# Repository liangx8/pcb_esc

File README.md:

# Electronic speed control(ESC)

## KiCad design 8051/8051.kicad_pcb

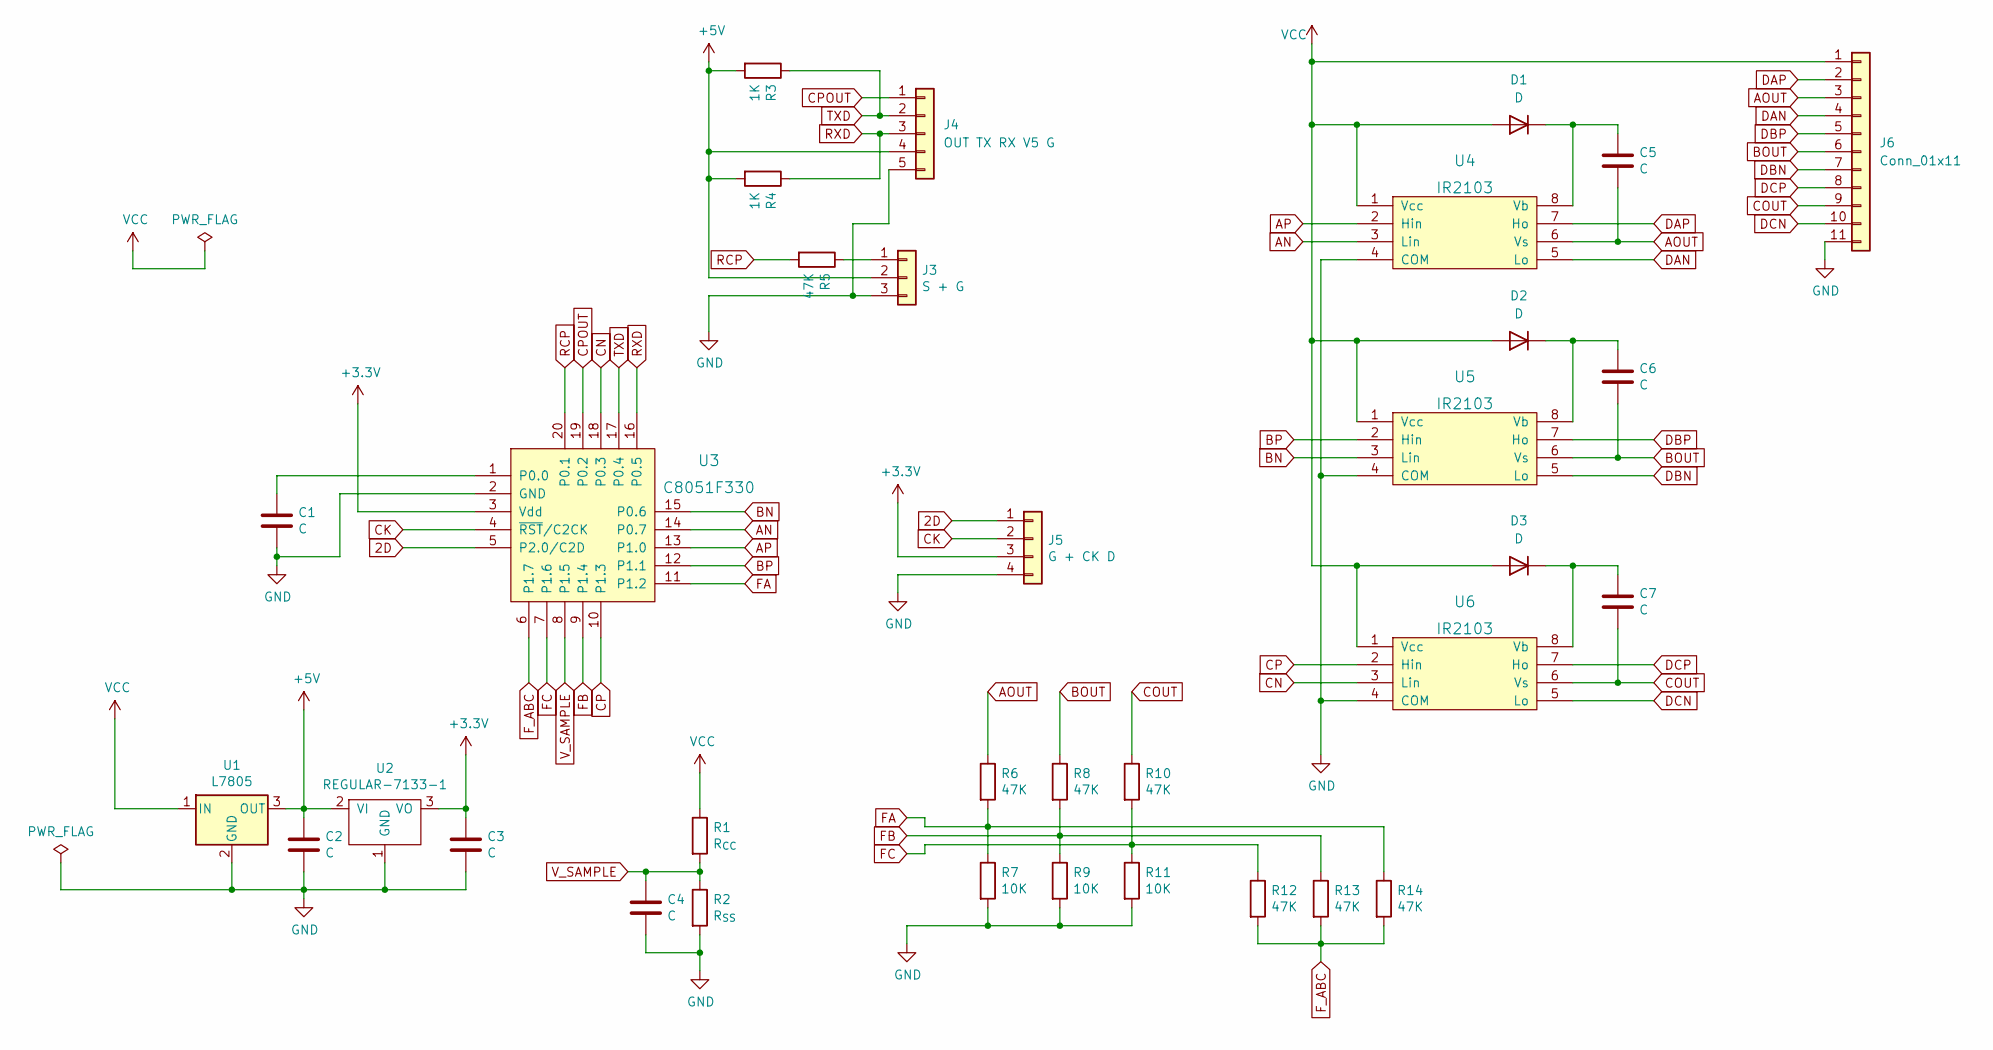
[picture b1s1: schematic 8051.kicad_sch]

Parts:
C1, C2, C3, C4: C; 0603_p1.7xpad1.0
C5, C6, C7: C; 0805_p2.0xpad1.0
D1, D2, D3: D; 0805_p2.0xpad1.0
J3: S + G; PinHeader_1x03_P2.54mm_Vertical
J4: OUT TX RX V5 G; PinHeader_1x05_P2.54mm_Vertical
J5: G + CK D; CONN4-P2.54-DR1.0-W1.5
J6: Conn_01x11; PinHeader_1x11_P2.54mm_Vertical
R1: R_{CC}; 0603_p1.7xpad1.0
R2: R_{SS}; 0603_p1.7xpad1.0
R3, R4: 1K; 0603_p1.7xpad1.0
R5, R6, R8, R10, R12, R13, R14: 47K; 0603_p1.7xpad1.0
R7, R9, R11: 10K; 0603_p1.7xpad1.0
U1: L7805; TO-252-2
U2: REGULAR-7133-1; SOT-89-3_Handsoldering
U3: C8051F330; QFN-20_EP_4x4_Pitch0.5mm
U4, U5, U6: IR2103; SOIC-8

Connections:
2D: J5.1, U3.5 (P2.0/C2D)
+3V3: C3.1, J5.3, U2.3 (VO), U3.3 (Vdd)
+5V: C2.1, J3.2, J4.4, R3.2, R4.2, U1.3 (OUT), U2.2 (VI)
AN: U3.14 (P0.7), U4.3 (Lin)
AOUT: C5.2, J6.3, R6.1, U4.6 (Vs)
AP: U3.13 (P1.0), U4.2 (Hin)
BN: U3.15 (P0.6), U5.3 (Lin)
BOUT: C6.2, J6.6, R8.1, U5.6 (Vs)
BP: U3.12 (P1.1), U5.2 (Hin)
CK: J5.2, U3.4 (~RST/C2CK)
CN: U3.18 (P0.3), U6.3 (Lin)
COUT: C7.2, J6.9, R10.1, U6.6 (Vs)
CP: U3.10 (P1.3), U6.2 (Hin)
CPOUT: J4.1, U3.19 (P0.2)
DAN: J6.4, U4.5 (Lo)
DAP: J6.2, U4.7 (Ho)
DBN: J6.7, U5.5 (Lo)
DBP: J6.5, U5.7 (Ho)
DCN: J6.10, U6.5 (Lo)
DCP: J6.8, U6.7 (Ho)
FA: R6.2, R7.1, R14.1, U3.11 (P1.2)
FB: R8.2, R9.1, R13.1, U3.9 (P1.4)
FC: R10.2, R11.1, R12.1, U3.7 (P1.6)
F_ABC: R12.2, R13.2, R14.2, U3.6 (P1.7)
GND: C1.2, C2.2, C3.2, C4.2, J3.3, J4.5, J5.4, J6.11, R2.2, R7.2, R9.2, R11.2, U1.2 (GND), U2.1 (GND), U3.2 (GND), U4.4 (COM), U5.4 (COM), U6.4 (COM)
unnamed: C1.1, U3.1 (P0.0)
unnamed: C5.1, D1.1 (K), U4.8 (Vb)
unnamed: C6.1, D2.1 (K), U5.8 (Vb)
unnamed: C7.1, D3.1 (K), U6.8 (Vb)
unnamed: J3.1, R5.1
RCP: R5.2, U3.20 (P0.1)
RXD: J4.3, R4.1, U3.16 (P0.5)
TXD: J4.2, R3.1, U3.17 (P0.4)
VCC: D1.2 (A), D2.2 (A), D3.2 (A), J6.1, R1.1, U1.1 (IN), U4.1 (Vcc), U5.1 (Vcc), U6.1 (Vcc)
V_SAMPLE: C4.1, R1.2, R2.1, U3.8 (P1.5)

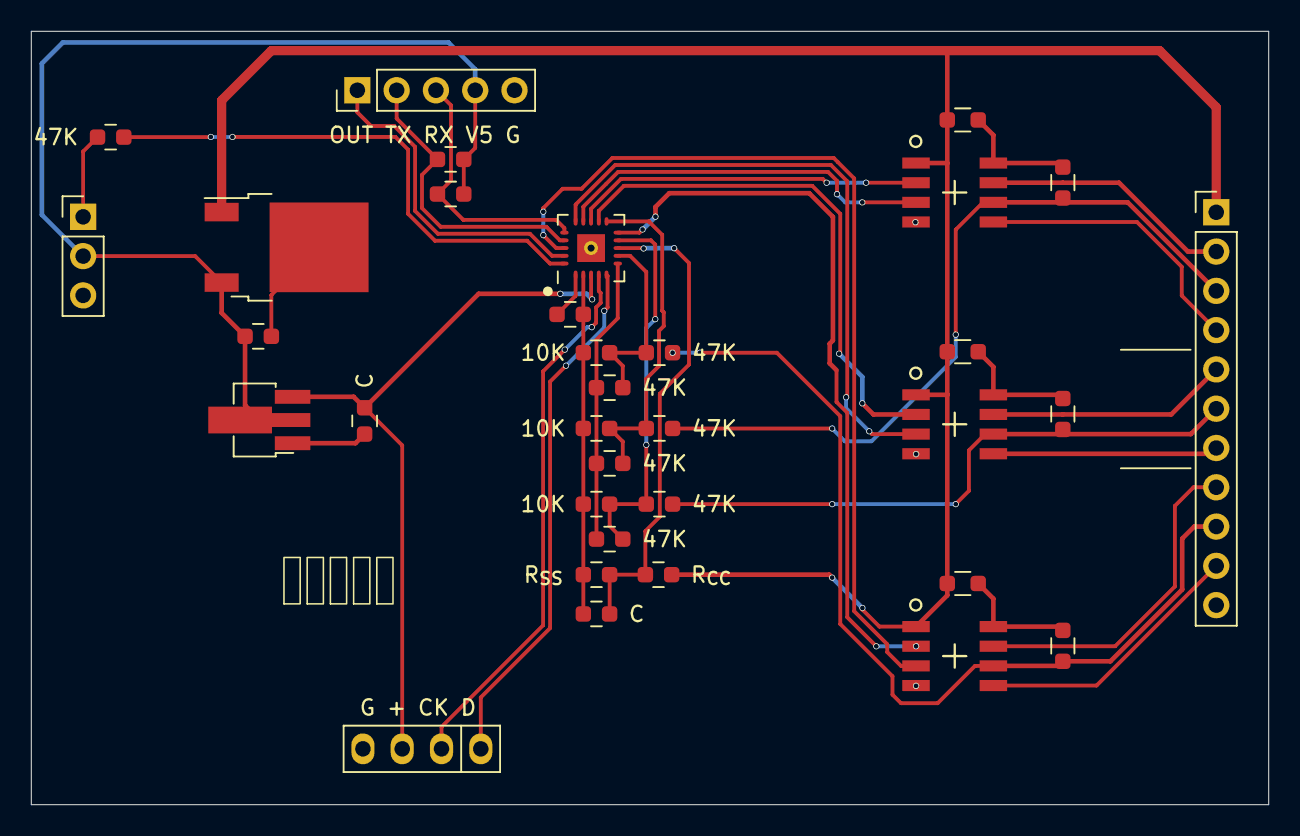
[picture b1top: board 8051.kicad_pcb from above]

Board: 2 copper layers, 80.0 x 50.0 mm, 34 parts (0 on the bottom side), 35 nets.

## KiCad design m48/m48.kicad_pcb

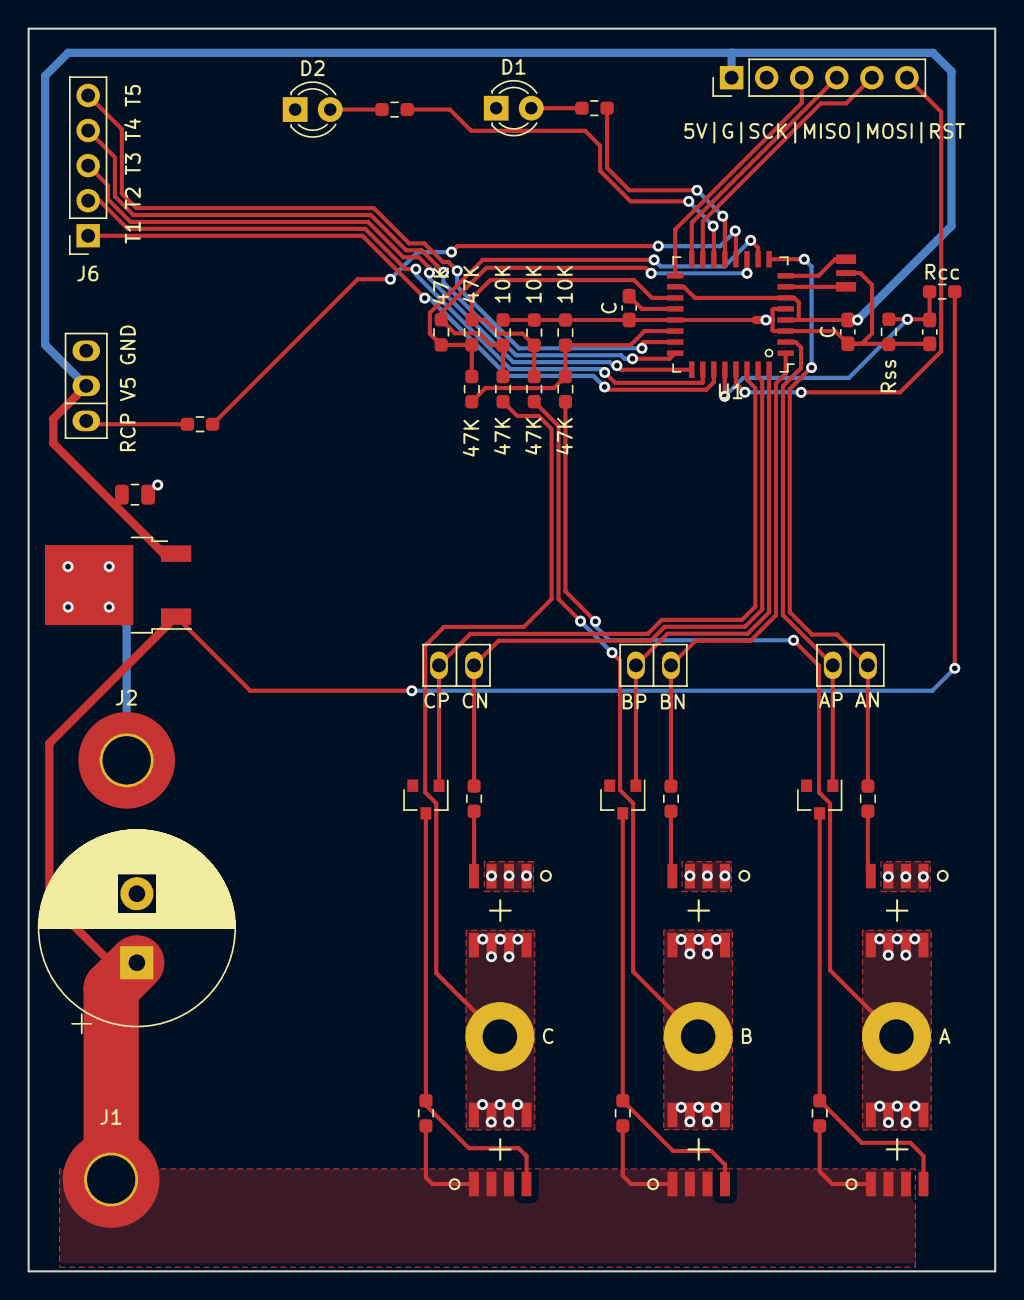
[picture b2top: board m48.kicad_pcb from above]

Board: 2 copper layers, 70.0 x 90.0 mm, 50 parts (0 on the bottom side), 41 nets.

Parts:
C1: C; CP_Radial_D14.0mm_P5.00mm
C2, C3, C4: C; C_0603_Pad1.08x0.95mm_HandSolder
C6: C; C_0805_2012Metric
D1, D2: LED; LED_D3.0mm
J1, J2: power-mount-hole; MountingHole_3.5mm_Pad_TopBottom
J3: A; MountingHole_2.5mm_Pad
J4: B; MountingHole_2.5mm_Pad
J5: C; MountingHole_2.5mm_Pad
J6: T1 T2 T3 T4 T5; PinSocket_1x05_P2.54mm_Vertical
J7: RCP V5 GND; CONN3-P2.54-DR1.0-W1.5
J8: AP AN; CONN2-P2.54-DR1.0-W1.3
J9: BP BN; CONN2-P2.54-DR1.0-W1.3
J10: CP CN; CONN2-P2.54-DR1.0-W1.3
J11: Conn_01x06; PinHeader_1x06_P2.54mm_Vertical
Q1, Q4, Q7: 2N3055; SOT-23
Q2, Q5, Q8: nfet; SOIC-8
Q3, Q6, Q9: pfet; SOIC-8
R2: Rcc; R_0603_Pad0.98x0.95mm_HandSolder
R3: Rss; R_0603_Pad0.98x0.95mm_HandSolder
R4, R6, R8, R10, R11, R12: 47K; R_0603_Pad0.98x0.95mm_HandSolder
R5, R7, R9: 10K; R_0603_Pad0.98x0.95mm_HandSolder
R13, R14, R15, R17, R19, R21: 1K; R_0603_Pad0.98x0.95mm_HandSolder
R16, R18, R20: R; R_0603_Pad0.98x0.95mm_HandSolder
U1: ATmega48P-20AU; QFP-32_8x8_Pitch0.8mm
U2: L7805; TO-252-2
Y1: Crystal_GND2; crystal_smd_3-1.45x2mm

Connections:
+5V: C2.1, C6.1, J7.2, J11.1, U1.4, U1.6, U1.18, U2.3
AN: J8.1, R16.2, U1.9
AP: J8.2, Q1.1, U1.2
BN: J9.1, R18.2, U1.1
BP: J9.2, Q4.1, U1.32
CN: J10.1, R20.2, U1.31
CP: J10.2, Q7.1, U1.30
Fa: R4.1, R5.2, R12.1, U1.22
Fabc: R10.2, R11.2, R12.2, U1.10
Fb: R6.1, R7.2, R11.1, U1.19
Fc: R8.1, R9.2, R10.1, U1.11
GND: C1.2, C2.2, C3.2, C4.2, C6.2, D1.1, D2.1, J2.1, J7.3, J11.2, Q1.2, Q2.1, Q2.2, Q2.3, Q4.2, Q5.1, Q5.2, Q5.3, Q7.2, Q8.1, Q8.2, Q8.3, R3.1, R5.1, R7.1, R9.1, U1.3, U1.5, U1.21, U2.2, Y1.2
LED1: R13.2, U1.13
LED2: R14.2, U1.14
MISO: J11.4, U1.16
MOSI: J11.5, U1.15
unnamed: C3.1, U1.20
unnamed: D1.2, R13.1
unnamed: D2.2, R14.1
unnamed: J7.1, R15.2
unnamed: Q1.3, Q3.4, R17.2
unnamed: Q2.4, R16.1
unnamed: Q4.3, Q6.4, R19.2
unnamed: Q5.4, R18.1
unnamed: Q7.3, Q9.4, R21.2
unnamed: Q8.4, R20.1
unnamed: U1.7, Y1.1
unnamed: U1.8, Y1.3
OUT_A: J3.1, Q2.5, Q2.6, Q2.7, Q2.8, Q3.5, Q3.6, Q3.7, Q3.8, R4.2
OUT_B: J4.1, Q5.5, Q5.6, Q5.7, Q5.8, Q6.5, Q6.6, Q6.7, Q6.8, R6.2
OUT_C: J5.1, Q8.5, Q8.6, Q8.7, Q8.8, Q9.5, Q9.6, Q9.7, Q9.8, R8.2
RCP: R15.1, U1.12
RESET: J11.6, U1.29
SCK: J11.3, U1.17
TEST1: J6.1, U1.27
TEST2: J6.2, U1.26
TEST3: J6.3, U1.25
TEST4: J6.4, U1.24
TEST5: J6.5, U1.23
VCC: C1.1, J1.1, Q3.1, Q3.2, Q3.3, Q6.1, Q6.2, Q6.3, Q9.1, Q9.2, Q9.3, R2.2, R17.1, R19.1, R21.1, U2.1
V_SAMPLE: C4.1, R2.1, R3.2, U1.28

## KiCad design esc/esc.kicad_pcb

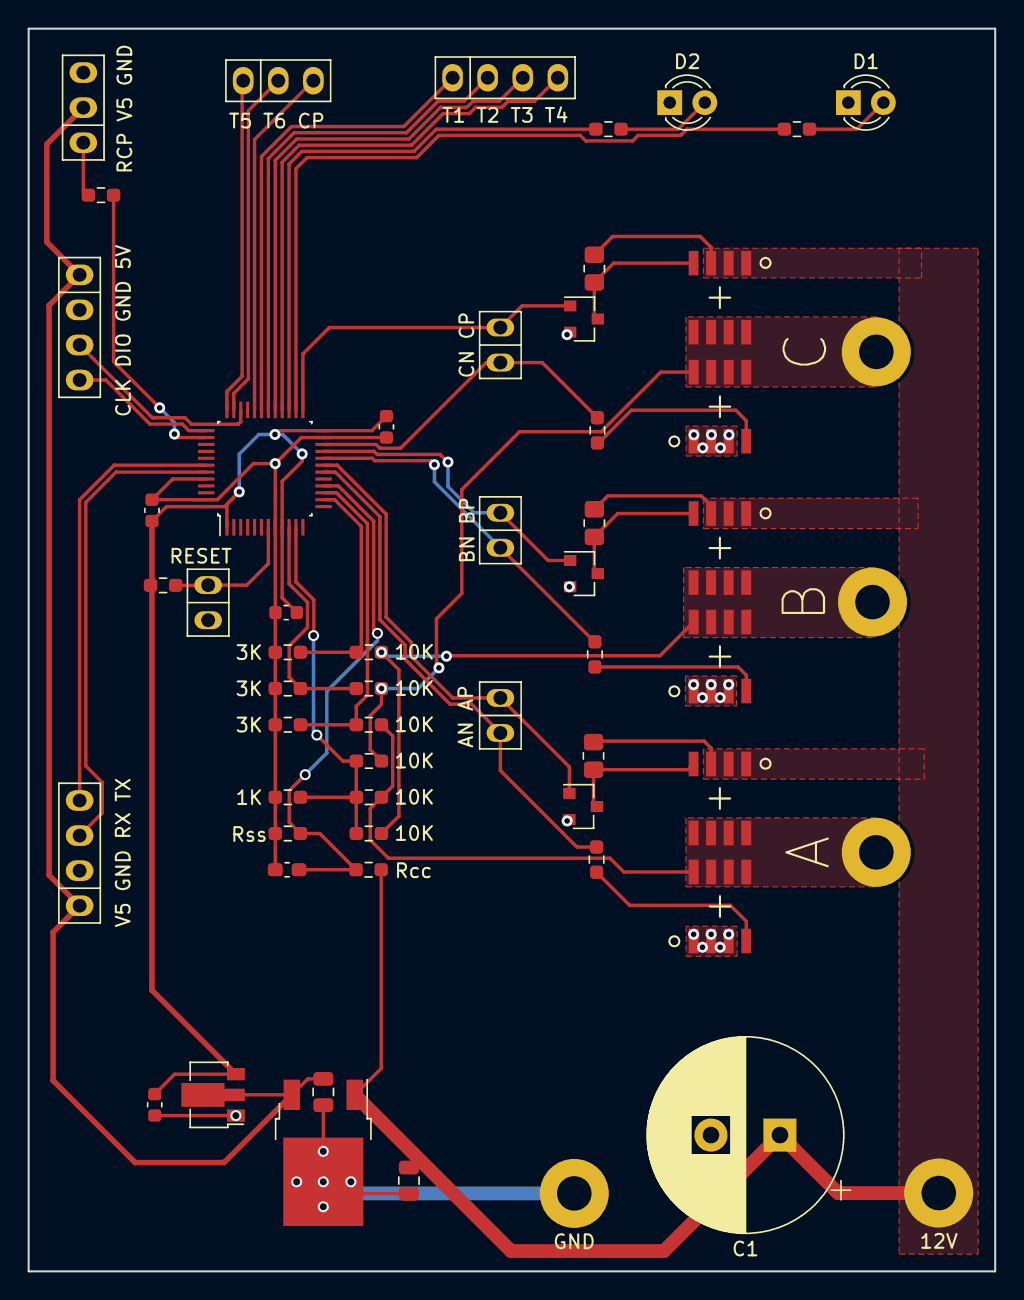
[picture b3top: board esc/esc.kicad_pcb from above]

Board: 2 copper layers, 70.0 x 90.0 mm, 58 parts (0 on the bottom side), 42 nets.

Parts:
C1: C; CP_Radial_D14.0mm_P5.00mm
C2: C; C_0603_1608Metric_Pad1.08x0.95mm_HandSolder
C3, C4, C5, C6: C; C_0603_1608Metric
C7, C8: C; C_0805_2012Metric
D1, D2: LED; LED_D3.0mm
J1: 12V; MountingHole_2.5mm_Pad
J2: GND; MountingHole_2.5mm_Pad
J3: A; MountingHole_2.5mm_Pad
J4: B; MountingHole_2.5mm_Pad
J5: C; MountingHole_2.5mm_Pad
J6: RESET; CONN2-P2.54-DR1.0-W1.3
J7: V5 GND RX TX; CONN4-P2.54-DR1.0-W1.5
J8: T1 T2 T3 T4; CONN4-P2.54-DR1.0-W1.5
J9: T5 T6 CP; CONN3-P2.54-DR1.0-W1.5
J10: RCP V5 GND; CONN3-P2.54-DR1.0-W1.5
J11: AN AP; CONN2-P2.54-DR1.0-W1.3
J12: BN BP; CONN2-P2.54-DR1.0-W1.3
J13: CN CP; CONN2-P2.54-DR1.0-W1.3
J14: CLK DIO GND 5V; CONN4-P2.54-DR1.0-W1.5
Q1, Q4, Q7: 2N3055; SOT-23
Q2, Q5, Q8: nfet; SOIC-8
Q3, Q6, Q9: pfet; SOIC-8
R1: Rcc; R_0603_1608Metric_Pad0.98x0.95mm_HandSolder
R2: Rss; R_0603_1608Metric_Pad0.98x0.95mm_HandSolder
R3, R5, R7, R9, R10, R13: 10K; R_0603_1608Metric_Pad0.98x0.95mm_HandSolder
R4, R6, R8: 3K; R_0603_1608Metric_Pad0.98x0.95mm_HandSolder
R11, R12, R14, R15, R16: 1K; R_0603_1608Metric_Pad0.98x0.95mm_HandSolder
R17, R19, R21: R; R_0603_1608Metric_Pad0.98x0.95mm_HandSolder
R18, R20, R22: 1K; R_0805_2012Metric_Pad1.20x1.40mm_HandSolder
U1: STM32F051C8Tx; QFP-48_P0.5mm_W0.22
U2: L7805; TO-252-2
U3: REGULAR-7133-1; SOT-89-3

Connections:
+3V3: C3.1, C4.1, C5.1, C6.1, R12.2, U1.1, U1.9, U1.24, U1.48, U3.3
+5V: C8.1, J7.1, J10.2, J14.1, U2.3, U3.2
AN: J11.2, R17.2, U1.18
AP: J11.1, Q1.1, U1.19
BN: J12.2, R19.2, U1.20
BP: J12.1, Q4.1, U1.21
CN: J13.2, R21.2, U1.22
CP: J13.1, Q7.1, U1.25
CPOUT: J9.3, U1.32
Fa: R3.1, R4.2, U1.15
Fabc: R9.1, R10.1, R11.2, R13.1, U1.11
Fb: R5.1, R6.2, U1.14
Fc: R7.1, R8.2, U1.10
GND: C1.2, C2.2, C3.2, C4.2, C5.2, C6.2, C7.2, C8.2, D1.1, D2.1, J2.1, J6.2, J7.2, J10.3, J14.2, Q1.2, Q2.1, Q2.2, Q2.3, Q4.2, Q5.1, Q5.2, Q5.3, Q7.2, Q8.1, Q8.2, Q8.3, R2.1, R4.1, R6.1, R8.1, R11.1, U1.8, U1.23, U1.44, U1.47, U2.2, U3.1
LED1: R14.2, U1.26
LED2: R15.2, U1.27
unnamed: D1.2, R14.1
unnamed: D2.2, R15.1
unnamed: J10.1, R16.2
unnamed: Q1.3, Q3.4, R18.2
unnamed: Q2.4, R17.1
unnamed: Q4.3, Q6.4, R20.2
unnamed: Q5.4, R19.1
unnamed: Q7.3, Q9.4, R22.2
unnamed: Q8.4, R21.1
OUT_A: J3.1, Q2.5, Q2.6, Q2.7, Q2.8, Q3.5, Q3.6, Q3.7, Q3.8, R3.2, R9.2
OUT_B: J4.1, Q5.5, Q5.6, Q5.7, Q5.8, Q6.5, Q6.6, Q6.7, Q6.8, R5.2, R10.2
OUT_C: J5.1, Q8.5, Q8.6, Q8.7, Q8.8, Q9.5, Q9.6, Q9.7, Q9.8, R7.2, R13.2
RCP: R16.1, U1.38
RESET: J6.1, R12.1, U1.7
RXD: J7.3, U1.43
SWCLK: J14.4, U1.37
SWDIO: J14.3, U1.34
TEST1: J8.1, U1.31
TEST2: J8.2, U1.30
TEST3: J8.3, U1.29
TEST4: J8.4, U1.28
TEST5: J9.1, U1.36
TEST6: J9.2, U1.35
TXD: J7.4, U1.42
VCC: C1.1, C7.1, J1.1, Q3.1, Q3.2, Q3.3, Q6.1, Q6.2, Q6.3, Q9.1, Q9.2, Q9.3, R1.2, R18.1, R20.1, R22.1, U2.1
V_SAMPLE: C2.1, R1.1, R2.2, U1.16

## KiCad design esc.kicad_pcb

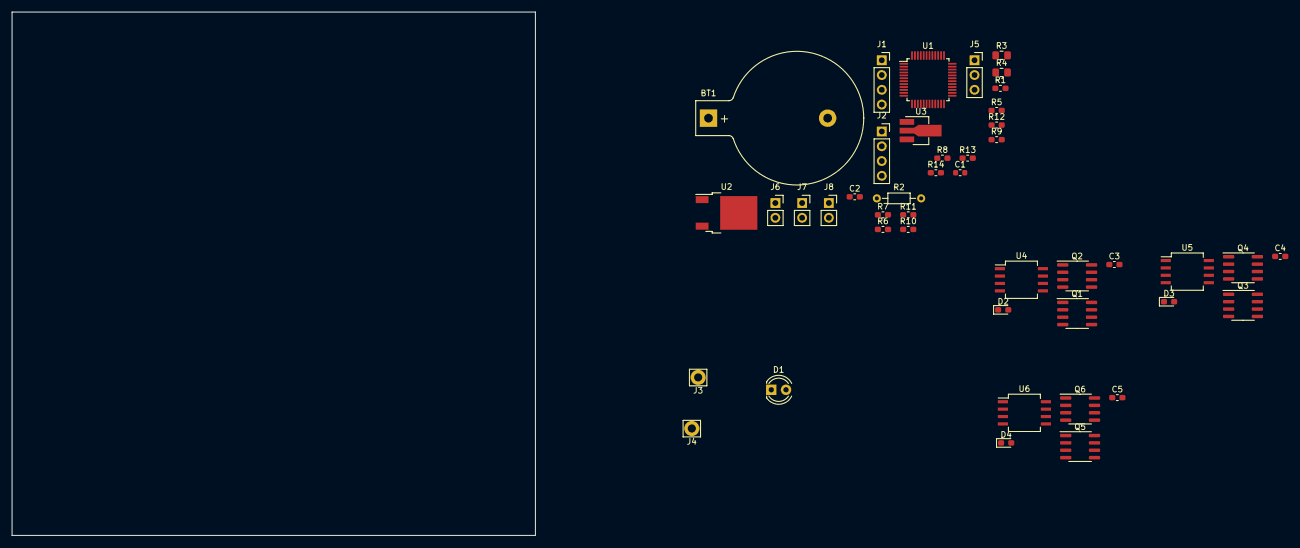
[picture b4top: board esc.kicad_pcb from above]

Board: 2 copper layers, 90.0 x 90.0 mm, 44 parts (0 on the bottom side), 37 nets, no tracks yet.

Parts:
BT1: Battery_Cell; BatteryHolder_Keystone_103_1x20mm
C1: C; C_0603_1608Metric
C2, C3, C4, C5: C; C_0603_1608Metric_Pad1.05x0.95mm_HandSolder
D1: LED; LED_D4.0mm
D2, D3, D4: D; D_0603_1608Metric_Pad1.05x0.95mm_HandSolder
J1, J2: Conn_01x04; PinSocket_1x04_P2.54mm_Vertical
J3, J4: Conn_01x01; Pin_D1.4mm_L8.5mm_W2.8mm_FlatFork
J5: Conn_01x03; PinSocket_1x03_P2.54mm_Vertical
J6, J7, J8: Conn_01x02; PinSocket_1x02_P2.54mm_Vertical
Q1, Q2, Q3, Q4, Q5, Q6: FDS2734; SOIC-8_3.9x4.9mm_P1.27mm
R1, R12: 1k; R_0603_1608Metric_Pad1.05x0.95mm_HandSolder
R2: 1K; R_Axial_DIN0204_L3.6mm_D1.6mm_P7.62mm_Horizontal
R3, R4: 2K; R_0805_2012Metric_Pad1.15x1.40mm_HandSolder
R5, R7, R9, R11, R13, R14: 20k; R_0603_1608Metric_Pad1.05x0.95mm_HandSolder
R6, R8, R10: 3k; R_0603_1608Metric_Pad1.05x0.95mm_HandSolder
U1: STM32F051C8Tx; LQFP-48_7x7mm_P0.5mm
U2: KA78M05_TO252; TO-252-2
U3: REGULAR-7133-1; SOT-89-3_Handsoldering
U4, U5, U6: IR2103; SO-8_5.3x6.2mm_P1.27mm

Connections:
+3V3: J1.1, J2.1, R1.2, U1.9, U1.24, U1.48, U3.3
+5V: J5.2, U2.3, U3.2
/AOUT: C5.2, Q5.1, Q5.2, Q5.3, Q6.5, Q6.6, Q6.7, Q6.8, R9.1, R11.1, U6.6
/BOUT: C3.2, Q1.1, Q1.2, Q1.3, Q2.5, Q2.6, Q2.7, Q2.8, R7.1, R13.1, U4.6
/COUT: C4.2, Q3.1, Q3.2, Q3.3, Q4.5, Q4.6, Q4.7, Q4.8, R5.1, R14.1, U5.6
/LED: R2.2, U1.22
/RXD: J2.3, U1.43
/SWCLK: J1.3, U1.37
/SWDIO: J1.4, U1.34
/TXD: J2.4, U1.42
AN: J6.2, U1.29, U6.3
AP: J6.1, U1.17, U6.2
BN: J7.2, U1.30, U4.3
BP: J7.1, U1.18, U4.2
CN: J8.2, U1.31, U5.3
CP: J8.1, U1.19, U5.2
Fa: R9.2, R10.1, U1.15
Fabc: R11.2, R12.1, R13.2, R14.2, U1.11
Fb: R7.2, R8.1, U1.14
Fc: R5.2, R6.1, U1.10
GND: BT1.2, C2.2, D1.1, J1.2, J2.2, J4.1, J5.3, Q2.1, Q2.2, Q2.3, Q4.1, Q4.2, Q4.3, Q6.1, Q6.2, Q6.3, R4.2, R6.2, R8.2, R10.2, R12.2, U1.8, U1.23, U1.44, U1.47, U2.2, U3.1, U4.4, U5.4, U6.4
unnamed: BT1.1, U1.1
unnamed: C1.1, J5.1
unnamed: C3.1, D2.1, U4.8
unnamed: C4.1, D3.1, U5.8
unnamed: C5.1, D4.1, U6.8
unnamed: D1.2, R2.1
unnamed: Q1.4, U4.7
unnamed: Q2.4, U4.5
unnamed: Q3.4, U5.7
unnamed: Q4.4, U5.5
unnamed: Q5.4, U6.7
unnamed: Q6.4, U6.5
unnamed: R1.1, U1.7
RCP: C1.2, U1.38
VCC: D2.2, D3.2, D4.2, J3.1, Q1.5, Q1.6, Q1.7, Q1.8, Q3.5, Q3.6, Q3.7, Q3.8, Q5.5, Q5.6, Q5.7, Q5.8, R3.1, U2.1, U4.1, U5.1, U6.1
V_SAMPLE: C2.1, R3.2, R4.1, U1.16

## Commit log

2019-11-07 init
2020-03-09 note.txt
2021-03-15 driverless motor
2021-03-17 imcomplete yet
2021-03-17 not done yet
2021-03-18 incomplete
2021-03-19 almost done
2021-03-21 confirm
2021-03-21 19号已经打样
2021-09-29 add atmel mega48
2021-09-29 default width 0.3mm
2021-10-08 working
2021-10-08 issued
2021-10-09 m48 esc 当日打样
2022-01-13 almost done(8051)
2022-01-13 准完成(8051)
2022-01-28 打样(8051)日期2022-01-16
2022-05-05 digital module
2022-05-13 已经打样，但是3伏和5伏的稳压没有做到地的过孔
